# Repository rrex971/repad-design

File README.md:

<?xml version="1.0" encoding="UTF-8" standalone="no"?>
<!DOCTYPE svg PUBLIC "-//W3C//DTD SVG 1.1//EN" "http://www.w3.org/Graphics/SVG/1.1/DTD/svg11.dtd">
<svg width="100%" height="100%" viewBox="0 0 1000 1000" version="1.1" xmlns="http://www.w3.org/2000/svg" xmlns:xlink="http://www.w3.org/1999/xlink" xml:space="preserve" xmlns:serif="http://www.serif.com/" style="fill-rule:evenodd;clip-rule:evenodd;stroke-linejoin:round;stroke-miterlimit:2;">
    <g transform="matrix(1.323706,0,0,1.323706,-186.401918,-115.643811)">
        <path d="M216.364,491.155L216.364,162.909L820.727,162.909L820.727,480.266C820.495,480.264 820.262,480.263 820.028,480.263C803.442,480.263 790.66,484.787 781.684,493.833C772.709,502.88 768.221,515.843 768.221,532.723C768.221,549.574 772.716,562.556 781.706,571.669C790.7,580.777 803.475,585.331 820.028,585.331C820.262,585.331 820.495,585.33 820.727,585.328L820.727,660.669C820.495,660.667 820.262,660.666 820.028,660.666C803.442,660.666 790.66,665.189 781.684,674.236C772.709,683.282 768.221,696.245 768.221,713.125C768.221,729.976 772.716,742.958 781.706,752.071C790.7,761.179 803.475,765.733 820.028,765.733C820.262,765.733 820.495,765.732 820.727,765.73L820.727,767.273L622.691,767.273C633.356,765.461 643.39,762.469 652.792,758.297C669.417,750.921 683.558,740.227 695.216,726.213C706.878,712.2 715.438,695.337 720.896,675.624L658.578,675.624C651.51,687.645 642.966,696.786 632.947,703.047C622.933,709.308 611.346,712.438 598.187,712.438C576.128,712.438 559.621,704.683 548.667,689.172C540.712,677.904 535.647,662.865 533.471,644.058L712.879,644.058C713.328,640.394 713.689,636.567 713.963,632.577C714.237,628.583 714.373,624.383 714.373,619.978C714.373,589.637 709.687,563.8 700.315,542.468C690.943,521.131 677.46,504.842 659.867,493.599C642.275,482.353 621.113,476.729 596.381,476.729C570.681,476.729 548.301,482.631 529.24,494.435C510.184,506.234 495.414,522.904 484.932,544.444C474.451,565.984 469.21,591.575 469.21,621.217C469.21,652.427 474.299,679.068 484.479,701.142C494.664,723.215 509.298,740.104 528.383,751.809C540.89,759.475 555.023,764.63 570.782,767.273L406.885,767.273L406.885,708.648L326.252,708.648L326.252,618.135C326.252,593.753 329.45,575.613 335.848,563.714C342.246,551.816 352.088,545.867 365.375,545.867C386.287,545.867 396.743,559.465 396.743,586.661L396.743,620.749L463.388,620.749L463.388,577.943C463.388,547.333 457.526,523.909 445.802,507.671C434.079,491.434 417.227,483.315 395.248,483.315C382.651,483.315 371.442,486.037 361.621,491.481C351.8,496.925 344.269,504.64 339.028,514.626L323.227,514.626L323.227,491.155L216.364,491.155ZM216.364,708.648L216.364,550.031L262.737,550.031L262.737,708.648L216.364,708.648ZM534.277,594.361C536.792,579.174 541.638,566.603 548.816,556.647C559.864,541.316 575.719,533.65 596.381,533.65C616.155,533.65 631.052,540.95 641.071,555.549C647.796,565.341 652.266,578.279 654.479,594.361L534.277,594.361Z" style="fill:rgb(255,255,255);"/>
    </g>
</svg>

# re:Pad Hardware Design
A 3-key Custom Hall Effect Keypad for osu! utilizing an RP2040-Zero base. Hardware Design Repo.
### _[Firmware Repo](https://github.com/rrex971/repad-firmware) | [Configurator Repo (pending)]()_

## Case Design
Designed to be as sleek as possible, as the previous version was found to be bulky both during gameplay and in general both by myself and others who've tested it. 
Since this version is a huge overhaul, I decided to go with a custom PCB reducing the Z-height by a lot, comparable to the [Wooting UwU](https://wooting.io/uwu) even, at just about 3cm keycap-to-base.

It's a two-part design (three if including the board itself), involving a base (top of which the PCB sits) and a top plate/case into which the switches click into.

## PCB/Controller Design
Designed in KiCad. First time trying out PCB design.
The custom PCB is designed with an RP2040-Zero in mind, with a footprint (credit: [CountParadox's KiCad Footprint](https://github.com/CountParadox/RP2040-Zero-Kicad)) that allows for an RP2040-Zero board to cleanly slot into. 

This saves a lot of effort and time with raw MCU interfacing being handled already, leaving the only soldering required to be simple THT components. SMD hall sensors would of course be ideal for such an implementation but unfortunately none as available as the TO-92 THT variant, so the slot cutouts are for the sensor legs to bend backwards and be flush with the board surface.

Similarly, the WS2812 RGB LEDs (one included on the RP2040-Zero package itself) had to be the THT variants due to component availability constraints. (though in this case it's a good thing since SMD LEDs seem like a pain to solder)

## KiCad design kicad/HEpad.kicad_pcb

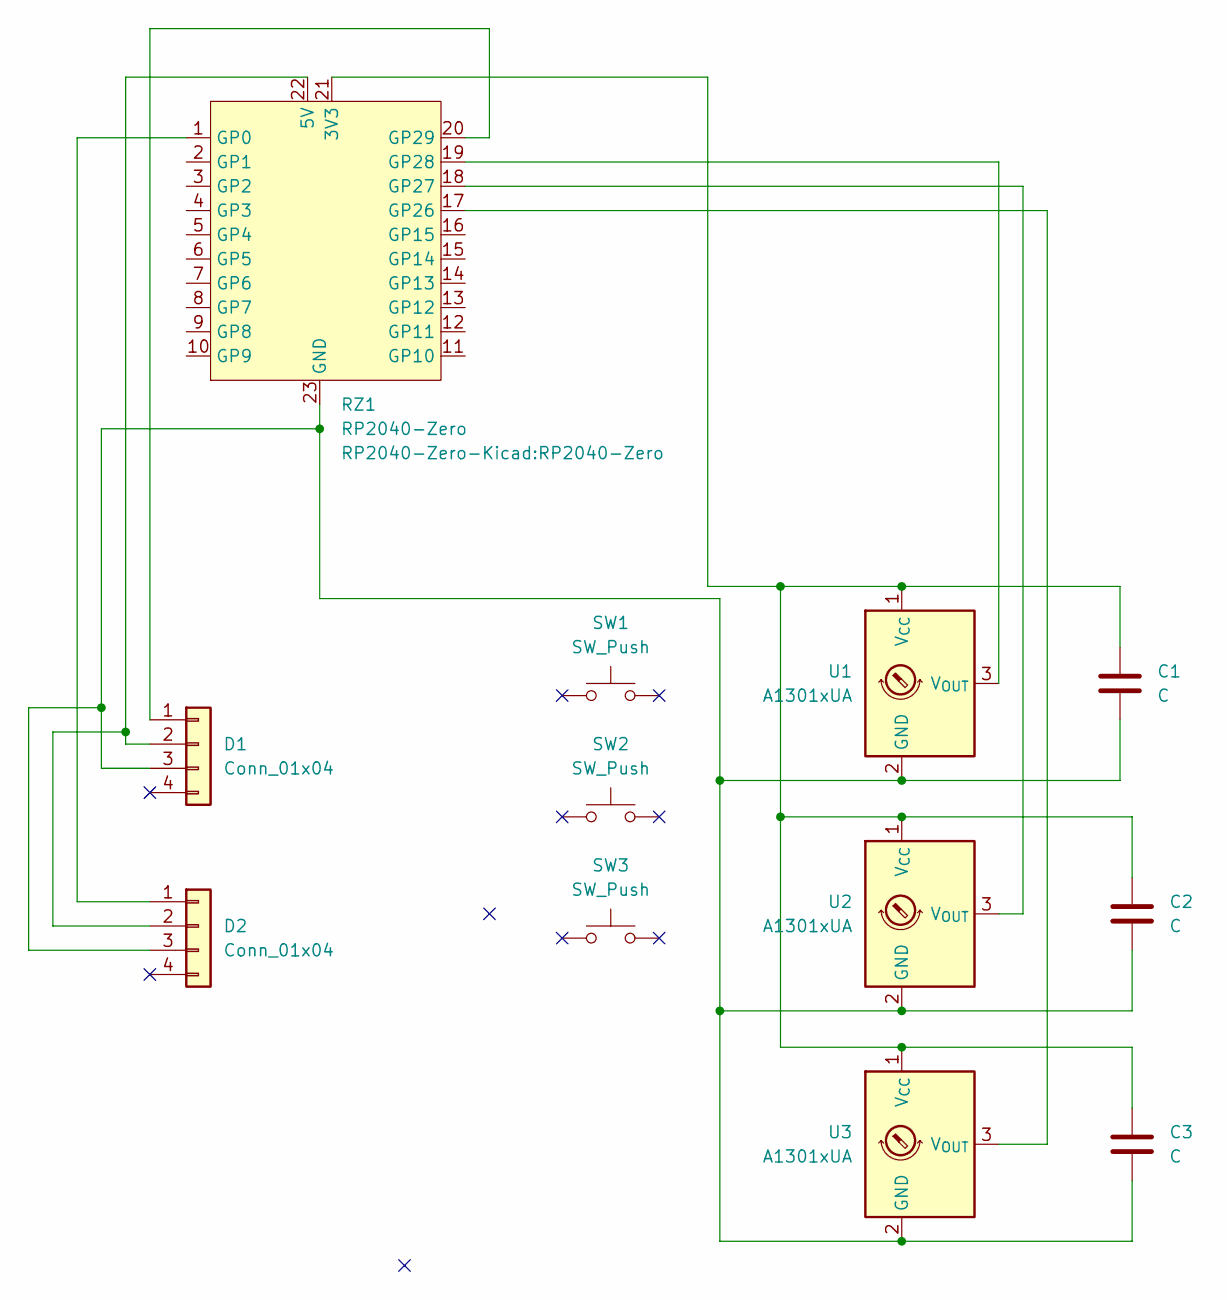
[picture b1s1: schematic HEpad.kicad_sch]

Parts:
C1, C2, C3: C; C_Disc_D3.0mm_W1.6mm_P2.50mm
D1, D2: Conn_01x04; PinHeader_1x04_P2.54mm_Vertical
RZ1: RP2040-Zero
SW1, SW2, SW3: SW_Push; SW_Cherry_MX_1.00u_PCB
U1, U2, U3: A1301xUA; TO-92_Inline

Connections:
unnamed: D1.1, RZ1.20 (GP29)
unnamed: D1.2, D2.2, RZ1.22 (5V)
unnamed: C1.2, C2.2, C3.2, D1.3, D2.3, RZ1.23 (GND), U1.2 (GND), U2.2 (GND), U3.2 (GND)
unnamed: D2.1, RZ1.1 (GP0)
unnamed: C1.1, C2.1, C3.1, RZ1.21 (3V3), U1.1 (V_{CC}), U2.1 (V_{CC}), U3.1 (V_{CC})
unnamed: RZ1.17 (GP26), U3.3 (V_{OUT})
unnamed: RZ1.18 (GP27), U2.3 (V_{OUT})
unnamed: RZ1.19 (GP28), U1.3 (V_{OUT})

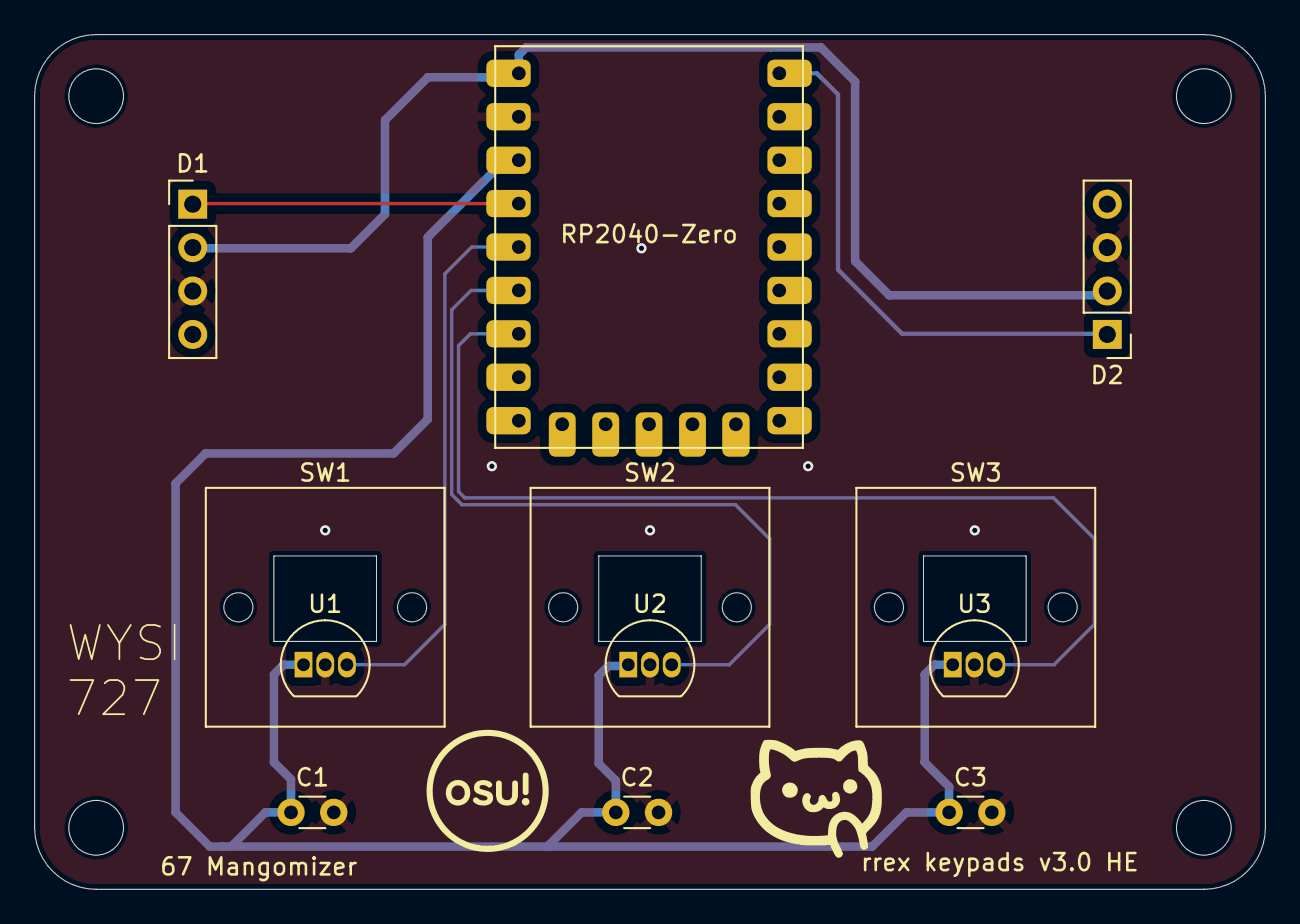
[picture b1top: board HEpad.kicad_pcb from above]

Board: 2 copper layers, 72.0 x 50.0 mm, 12 parts (0 on the bottom side), 8 nets.

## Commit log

2025-12-30 Initial commit: KiCad design files for HEpad
2026-04-24 Initial README
    true
2026-04-24 Update firmware repo link in README
2026-04-24 Fix stylizing of name.
